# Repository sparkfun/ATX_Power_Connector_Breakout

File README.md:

SparkFun ATX Power Connector Breakout - 12V/5V (4-pin)
========================================

<table class="table table-hover table-striped table-bordered">
  <tr align="center">
   <td></td>
   <td></td>
  </tr>
  <tr align="center">
    <td><i>SparkFun ATX Power Connector Breakout - 12V/5V (4-pin) <a href="https://www.sparkfun.com/products/15035">(BOB-15035)</a></i></td>
    <td><i>SparkFun ATX Power Connector Breakout Kit - 12V/5V (4-pin) <a href="https://www.sparkfun.com/products/15701">(KIT-15701)</a></i></td>
  </tr>
</table>

Do you need to power a project with 12V and 5V from one power supply? The ATX power connector breakout board breaks out the standard 4-pin computer peripheral port when mated with an ATX connector [(PRT-15700)](https://www.sparkfun.com/products/15700) for your 12V and 5V devices! Once you have chosen a power supply (whether it be an ATX power supply or the 12V/5V wall adapter), you're ready to give your project some life! This kit has everything you need (including a 12V/5V power supply) to solder together an ATX breakout and screw terminals to power your project directly or pump power into a breadboard using standard headers. 

ATX power supplies usually have a number of power connectors available to power components for a desktop computer.  One of these connectors is the 4-pin power connector, which is intended to power 12V and 5V computer peripherals (such as disk drives). Depending on the manufacturer of the power supply, the quantity of each connector can vary. If you want to easily grab some juice for your project from this connector, you'll need to connect the breakout board to this port.

**Note:** For the kit version, assembly and a basic knowledge of soldering will be required. The ATX power connector breakout does not come pre-assembled.

Repository Contents
-------------------

* **/Documentation** - Data sheets, additional product information
* **/Hardware** - Eagle design files (.brd, .sch)

Documentation
-------------------

* **[Hookup Guide](https://learn.sparkfun.com/tutorials/atx-power-connector-4-pin-breakout-hookup-guide)**
* **[Fritzing Part](https://github.com/sparkfun/Fritzing_Parts/blob/main/products/15035-sfe_ATX_Power_Connector_Breakout_12V_5V_Power_Supply.fzpz)**

Product Versions
----------------
* [KIT-15035](https://www.sparkfun.com/products/15701)
* [BOB-15035](https://www.sparkfun.com/products/15035)

License Information
-------------------

This product is _**open source**_! 

Please review the LICENSE.md file for license information. 

If you have any questions or concerns on licensing, please contact technical support on our [SparkFun forums](https://forum.sparkfun.com/viewforum.php?f=152).

Distributed as-is; no warranty is given.

- Your friends at SparkFun.

_<COLLABORATION CREDIT>_

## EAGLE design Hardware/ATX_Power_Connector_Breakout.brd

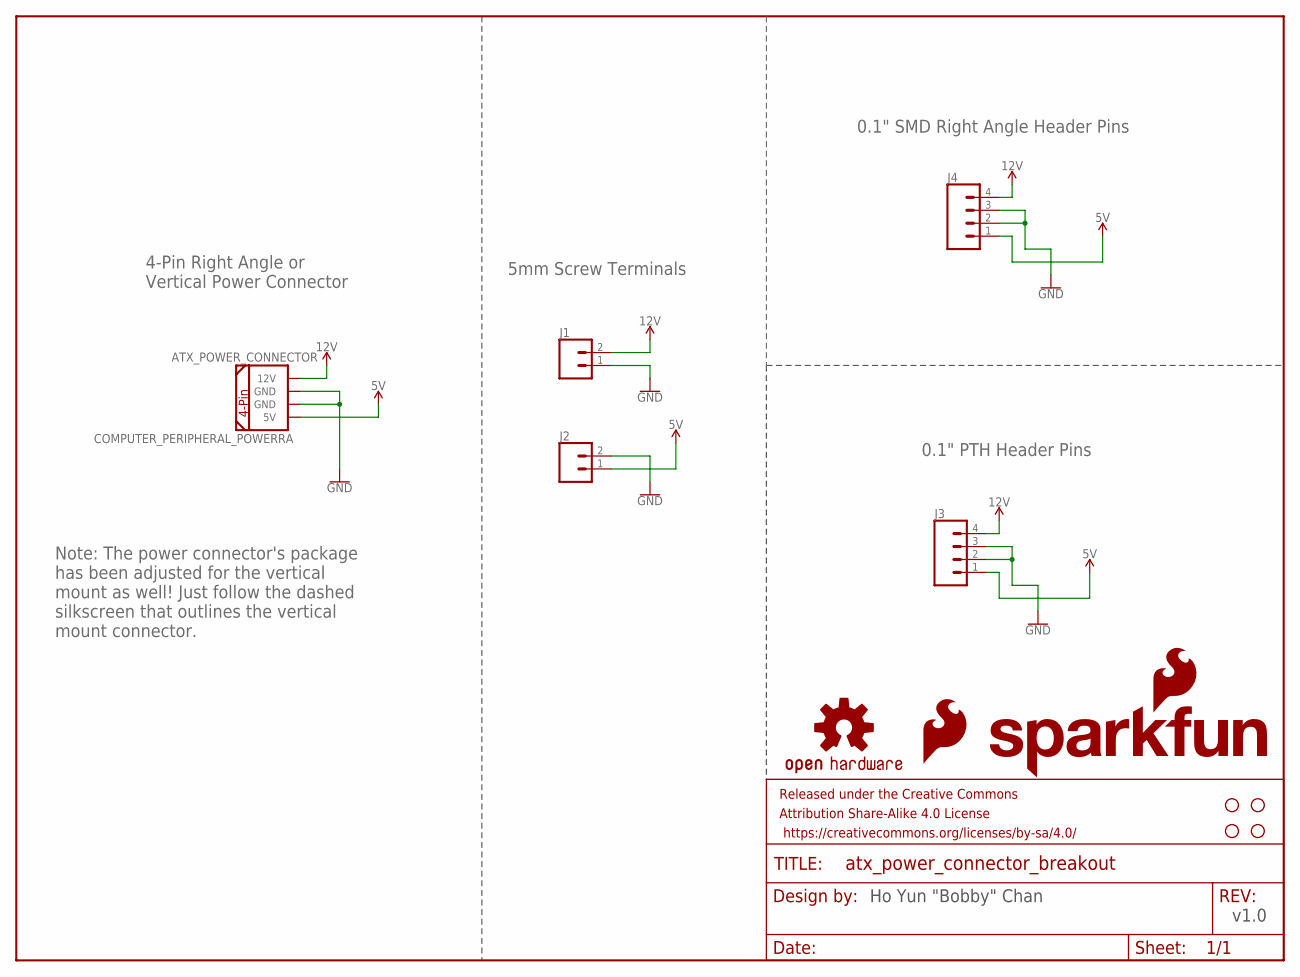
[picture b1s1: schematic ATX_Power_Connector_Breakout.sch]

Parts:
ATX_POWER_CONNECTOR: COMPUTER_PERIPHERAL_POWERRA; COMPUTER-PERIPHERAL-POWER-RA
FRAME1: FRAME-LETTER; CREATIVE_COMMONS
H1, H2, H3, H4: STAND-OFF
J1, J2: CONN_025MM; SCREWTERMINAL-5MM-2
J3: CONN_04; 1X04
J4: CONN_04SMD; 1X04_SMD_RA_MALE
LOGO1: OSHW-LOGOS; OSHW-LOGO-S
LOGO2: SFE_LOGO_NAME_FLAME.1_INCH; SFE_LOGO_NAME_FLAME_.1
LOGO3: SFE_LOGO_FLAME.1_INCH; SFE_LOGO_FLAME_.1

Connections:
5V: ATX_POWER_CONNECTOR.5V, J2.1, J3.1, J4.1
12V: ATX_POWER_CONNECTOR.12V, J1.2, J3.4, J4.4
GND: ATX_POWER_CONNECTOR.GND@1 (GND), ATX_POWER_CONNECTOR.GND@2 (GND), J1.1, J2.2, J3.2, J3.3, J4.2, J4.3

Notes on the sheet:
Ho Yun "Bobby" Chan
v1.0
5mm Screw Terminals
0.1" PTH Header Pins
4-Pin Right Angle or Vertical Power Connector
0.1" SMD Right Angle Header Pins
Note: The power connector's package has been adjusted for the vertical mount as well! Just follow the dashed silkscreen that outlines the vertical mount connector.

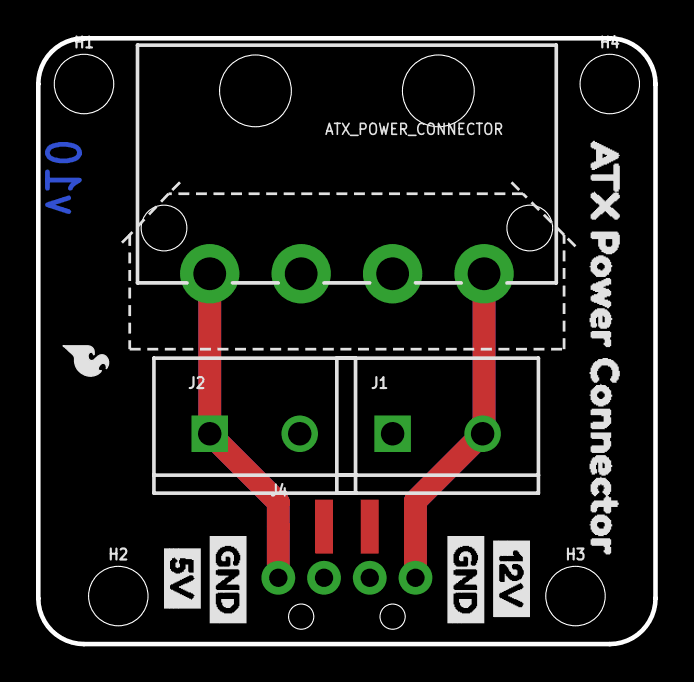
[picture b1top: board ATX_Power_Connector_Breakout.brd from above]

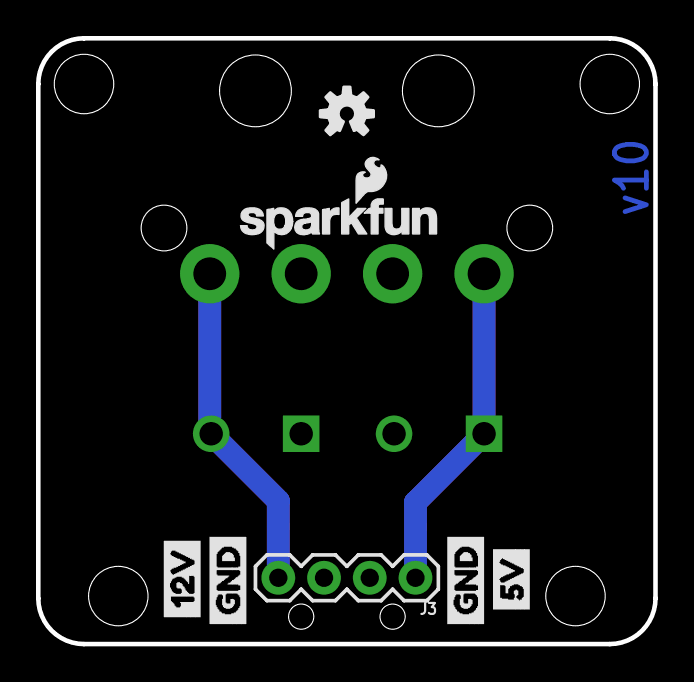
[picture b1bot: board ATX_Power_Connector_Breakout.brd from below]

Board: 2 copper layers, 34.3 x 33.7 mm, 22 parts (7 on the bottom side), 3 nets.

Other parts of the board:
U$1, U$5: 12V0
U$2, U$8: 5V0
U$3, U$4, U$6, U$7: GND0
U$9: ATX_POWER_CONNECTOR0

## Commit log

2018-07-03 Add Initial Eagle Files
2019-03-19 Update Board File
    -update text to standard buzzard
    -remove negasilk and replace with dashed outline of straight molex connector
    -add top thick trace on top
    -adjust package so that NC is GND
    -remove jumper on bottom of board
    -adjust size so mounting holes are not in the way of right angle connector
2019-03-25 Update Board
    -use buzzard text for board's name
    -adjust ground pour "width" to 0.01" to fit SparkFun DRC standards
2019-04-02 Update Text
    - Adjust ratio based on SFE text standards
    - Adjust sections in schematic for aesthetics
2019-04-05 Shorten Length of Voltage Rails
2019-04-05 Update Molex_Breakout_Board.sch
    Approve schematic error
2019-05-30 Update Molex_Breakout_Board.brd
    - Update Molex through holes for straight connector
    - adjust 5mm screw terminal spacing when slide-locking them together
    - reroute traces based on adjustments
2019-05-30 Update README.md
    - add storefront name and SKU
2019-08-19 Update Molex Connector Package
    - Move Straight Connector Silkscreen into RA connector package
    - Adjust Dill Hit of package to about 1.82 mm for straight connector for more tolerance depending on supplier
2019-08-19 Update Molex_Breakout_Board.sch
    - Add Note for vertical mount molex connector
2019-08-27 Rename Board and Files
2019-08-27 Rename File
2019-08-28 Update ATX_Power_Connector_Breakout.brd
    - move two mounting holes for Qwiic 1"x1"
    - adjust silkscreen for product name font size
2019-09-27 Add Dimensions
2019-10-22 Update Device
    - Update device to link to latest SparkFun Eagle's Connector Library

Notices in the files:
parts and their libraries:
SparkFun-Aesthetics: Licensing: Creative Commons ShareAlike 4.0 International - https://creativecommons.org/licenses/by-sa/4.0
SparkFun-Aesthetics: Released under the Creative Commons Attribution Share-Alike 4.0 License
SparkFun-Aesthetics: https://creativecommons.org/licenses/by-sa/4.0
